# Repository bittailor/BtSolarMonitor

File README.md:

# IoT Solar Monitor

Work in progress for my [Open IoT Challenge 2.0 project](http://open-iot-challenge.bittailor.ch/edition/second/)

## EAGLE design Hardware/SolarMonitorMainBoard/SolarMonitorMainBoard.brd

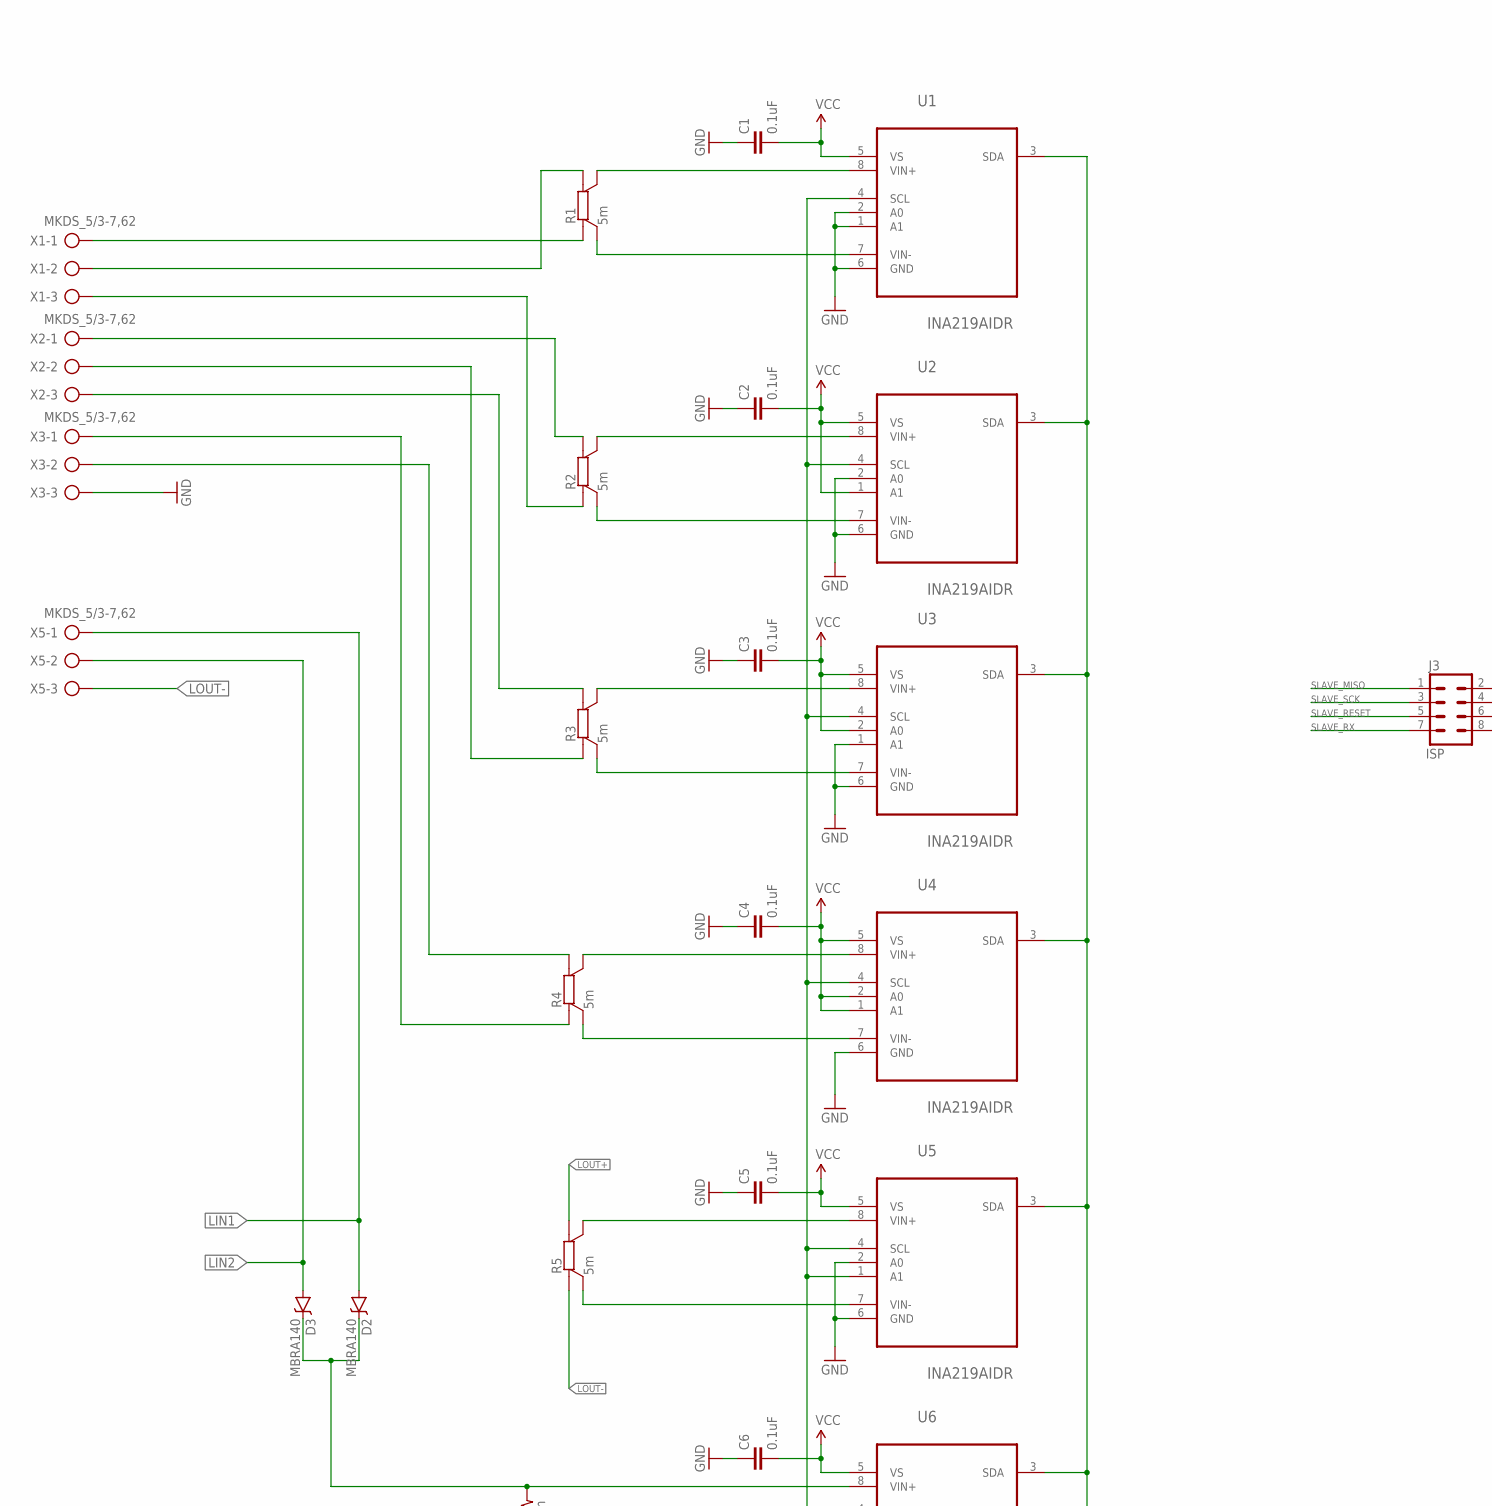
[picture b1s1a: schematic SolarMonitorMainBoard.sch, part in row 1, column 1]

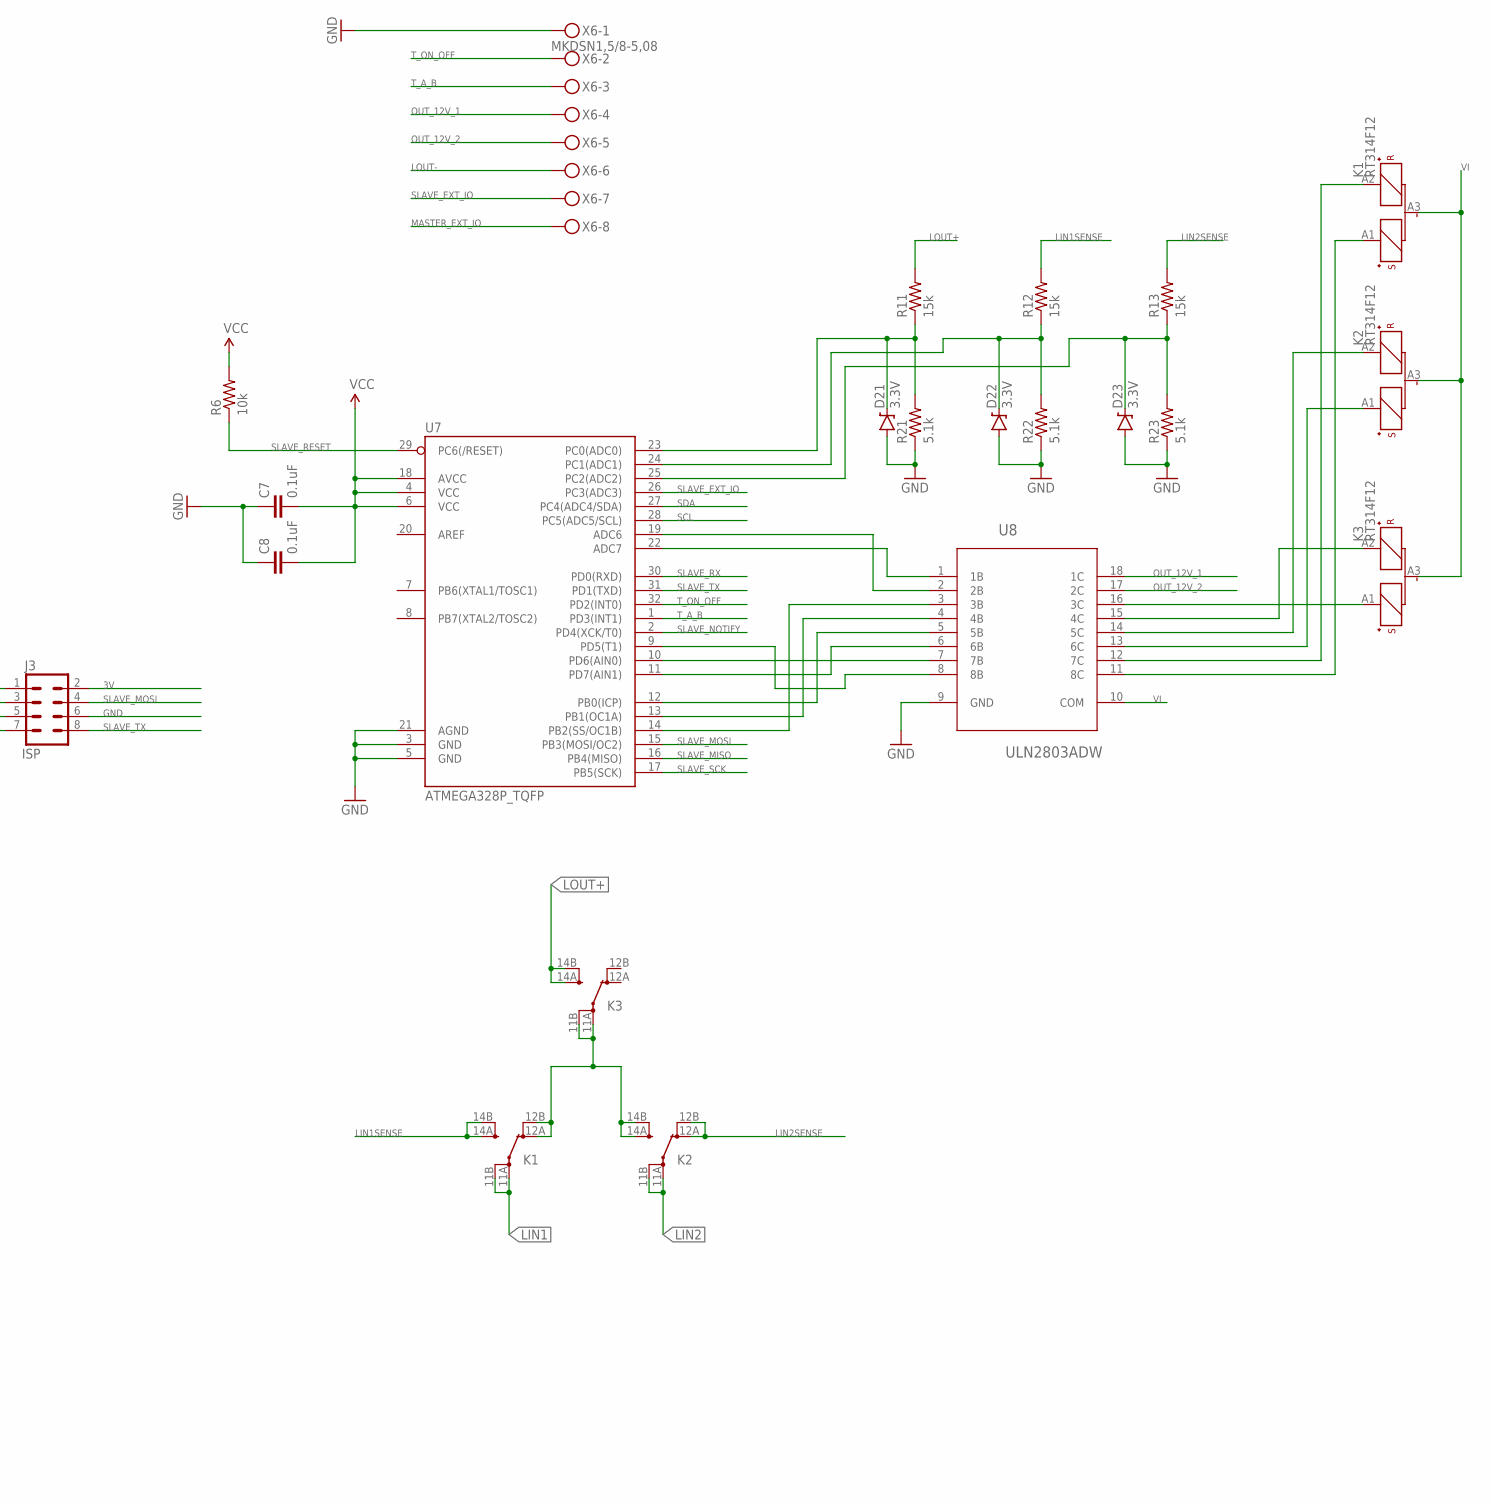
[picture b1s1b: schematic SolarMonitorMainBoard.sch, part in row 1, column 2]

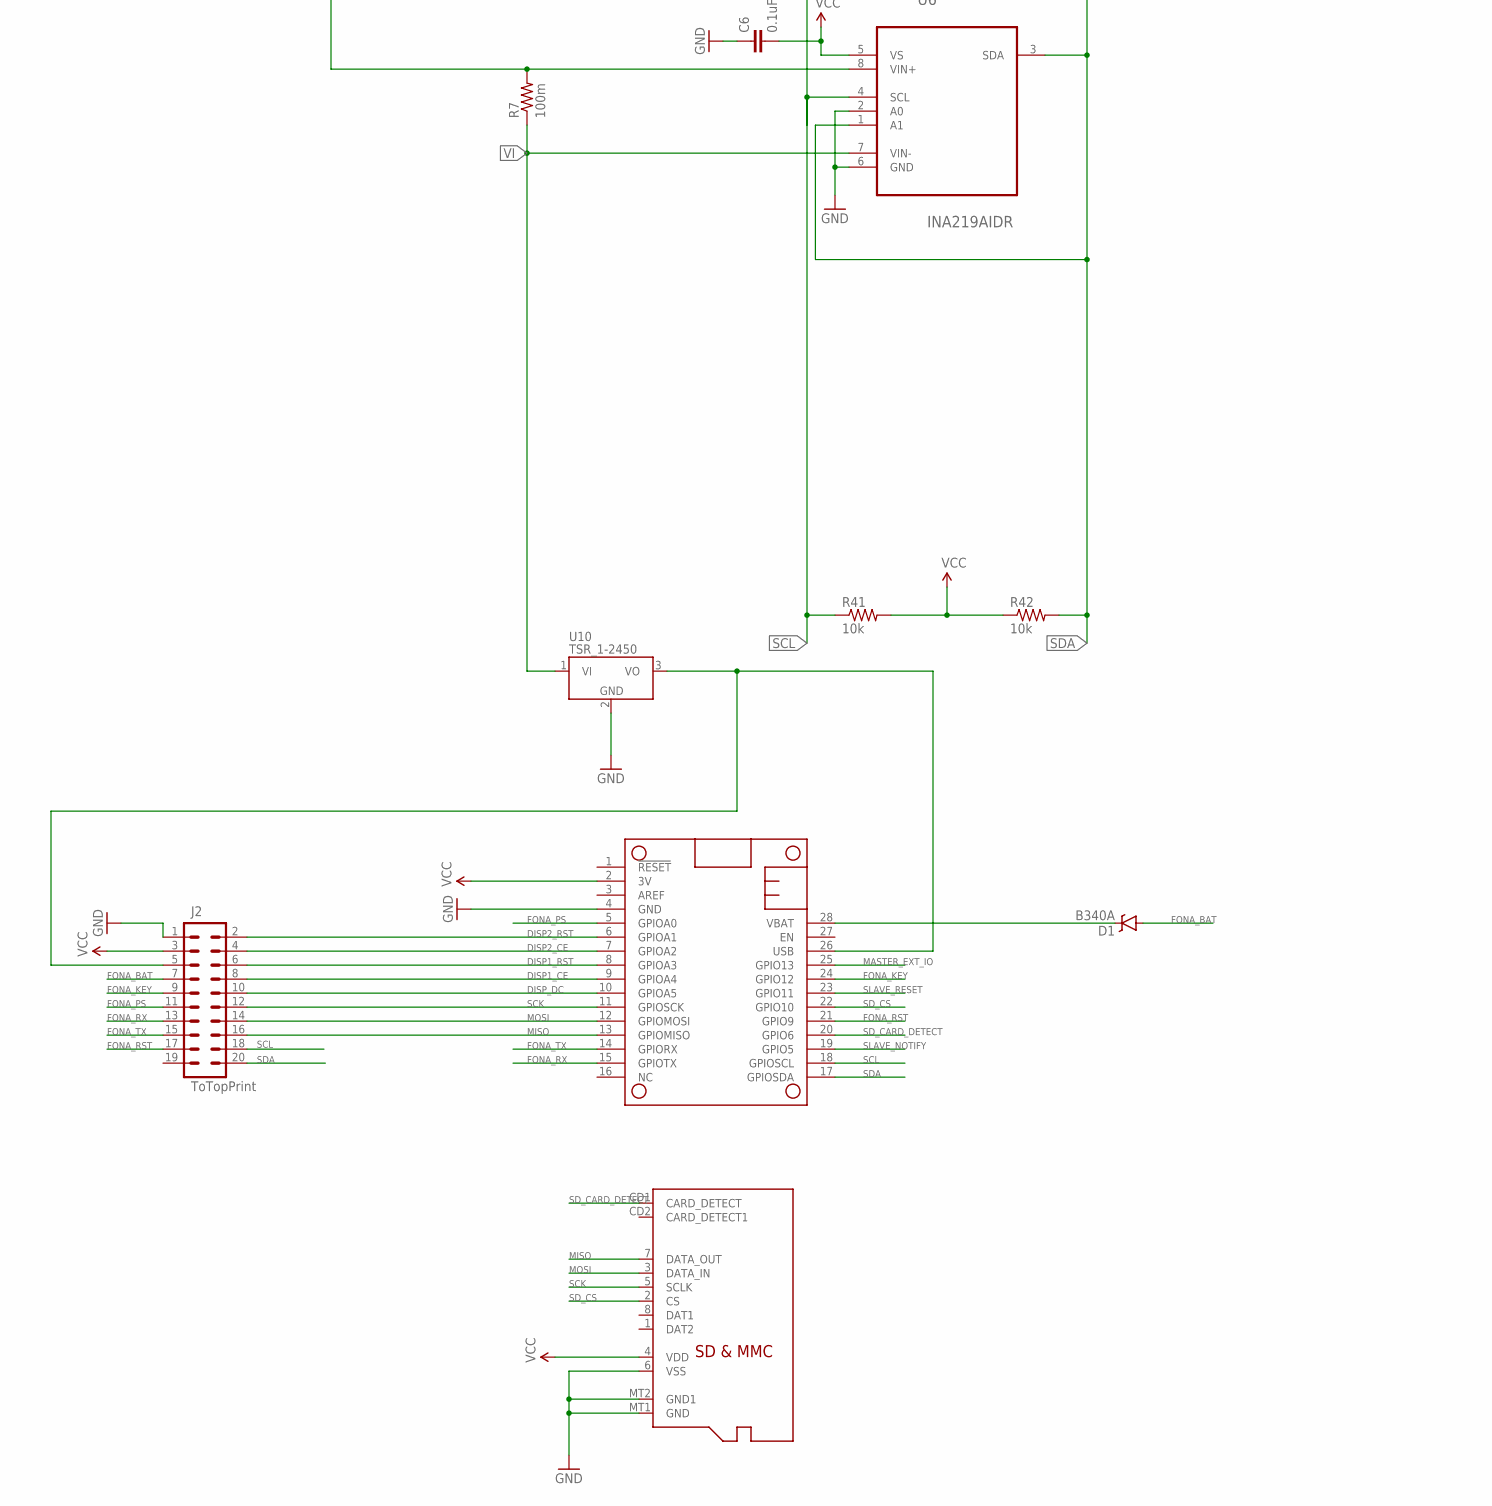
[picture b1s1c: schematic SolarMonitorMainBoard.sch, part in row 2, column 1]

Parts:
C1, C2, C3, C4, C5, C6, C7, C8: 0.1uF; 0805
D1: B340A; SMA-DIODE
D2, D3: MBRA140; SMA-DIODE
D21, D22, D23: 3.3V; SOD-323
J2: ToTopPrint; 2X10
J3: ISP; 2X4
K1, K2, K3: RT314F12; RT1-BI
MS1: FEATHERWING_NODIM; FEATHERWING_DIM
R1, R2, R3, R4, R5: 5m; SMV
R6, R41, R42: 10k; 0805
R7: 100m; R2512
R11, R12, R13: 15k; 0805
R21, R22, R23: 5.1k; 0805
U1, U2, U3, U4, U5, U6: INA219AIDR; SOIC127P600X175-8N
U7: ATMEGA328P_TQFP; TQFP32-08
U8: ULN2803ADW; SOIC127P1030X265-18N
U10: TSR_1-2450; TSR-1
U$1: MICROSD
X1, X2, X3, X5: MKDS_5/3-7,62; MKDS_5/3-762
X6: MKDSN1,5/8-5,08

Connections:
1VIN+: R1.I1 (A), X1.2
1VIN-: R1.I2 (B), X1.1
3V: C1.2, C2.2, C3.2, C4.2, C5.2, C6.2, C7.2, C8.2, J2.3, J3.2, MS1.2 (3V), R6.2, R41.2, R42.1, U1.5 (VS), U2.1 (A1), U2.5 (VS), U3.2 (A0), U3.5 (VS), U4.1 (A1), U4.2 (A0), U4.5 (VS), U5.5 (VS), U6.5 (VS), U7.4 (VCC), U7.6 (VCC), U7.18 (AVCC), U$1.4 (VDD)
5V: J2.5, MS1.26 (USB), U10.3 (VO)
DISP1_CE: J2.8, MS1.9 (GPIOA4)
DISP1_RST: J2.6, MS1.8 (GPIOA3)
DISP2_CE: J2.4, MS1.7 (GPIOA2)
DISP2_RST: J2.2, MS1.6 (GPIOA1)
DISP_DC: J2.10, MS1.10 (GPIOA5)
FONA_BAT: D1.A, J2.7
FONA_KEY: J2.9, MS1.24 (GPIO12)
FONA_PS: J2.11, MS1.5 (GPIOA0)
FONA_RST: J2.17, MS1.21 (GPIO9)
FONA_RX: J2.13, MS1.15 (GPIOTX)
FONA_TX: J2.15, MS1.14 (GPIORX)
GND: C1.1, C2.1, C3.1, C4.1, C5.1, C6.1, C7.1, C8.1, D21.A, D22.A, D23.A, J2.1, J3.6, MS1.4 (GND), R21.1, R22.1, R23.1, U1.1 (A1), U1.2 (A0), U1.6 (GND), U2.2 (A0), U2.6 (GND), U3.1 (A1), U3.6 (GND), U4.6 (GND), U5.2 (A0), U5.6 (GND), U6.2 (A0), U6.6 (GND), U7.3 (GND), U7.5 (GND), U7.21 (AGND), U8.9 (GND), U10.2 (GND), U$1.6 (VSS), U$1.MT1 (GND), U$1.MT2 (GND1), X3.3, X6.1
LIN1: D2.A, K1.11A (PA), K1.11B (PB), X5.1
LIN1SENSE: K1.14A (SA), K1.14B (SB), R12.2
LIN2: D3.A, K2.11A (PA), K2.11B (PB), X5.2
LIN2SENSE: K2.12A (OA), K2.12B (OB), R13.2
LOUT+: K3.14A (SA), K3.14B (SB), R5.I1 (A), R11.2
LOUT-: R5.I2 (B), X5.3, X6.6
MASTER_EXT_IO: MS1.25 (GPIO13), X6.8
MISO: J2.16, MS1.13 (GPIOMISO), U$1.7 (DATA_OUT)
MOSI: J2.14, MS1.12 (GPIOMOSI), U$1.3 (DATA_IN)
unnamed: R2.I2 (B), X1.3
unnamed: D21.C, R11.1, R21.2, U7.23 (PC0(ADC0))
unnamed: U7.9 (PD5(T1)), U8.8 (8B)
unnamed: R2.I1 (A), X2.1
unnamed: R3.I1 (A), X2.3
unnamed: R3.I2 (B), X2.2
unnamed: R4.I2 (B), X3.1
unnamed: R4.I1 (A), X3.2
unnamed: D2.C, D3.C, R7.2, U6.8 (VIN+)
unnamed: U7.10 (PD6(AIN0)), U8.7 (7B)
unnamed: R2.U1 (SA), U2.8 (VIN+)
unnamed: R2.U2 (SB), U2.7 (VIN-)
unnamed: R1.U1 (SA), U1.8 (VIN+)
unnamed: R1.U2 (SB), U1.7 (VIN-)
unnamed: R3.U1 (SA), U3.8 (VIN+)
unnamed: R3.U2 (SB), U3.7 (VIN-)
unnamed: R4.U1 (SA), U4.8 (VIN+)
unnamed: R4.U2 (SB), U4.7 (VIN-)
unnamed: R5.U1 (SA), U5.8 (VIN+)
unnamed: R5.U2 (SB), U5.7 (VIN-)
unnamed: U7.11 (PD7(AIN1)), U8.6 (6B)
unnamed: K1.12A (OA), K1.12B (OB), K2.14A (SA), K2.14B (SB), K3.11A (PA), K3.11B (PB)
unnamed: U7.12 (PB0(ICP)), U8.5 (5B)
unnamed: U7.13 (PB1(OC1A)), U8.4 (4B)
unnamed: U7.14 (PB2(SS/OC1B)), U8.3 (3B)
unnamed: U7.22 (ADC7), U8.1 (1B)
unnamed: U7.19 (ADC6), U8.2 (2B)
unnamed: K2.A1 (S+), U8.13 (6C)
unnamed: K2.A2 (R+), U8.14 (5C)
unnamed: D22.C, R12.1, R22.2, U7.24 (PC1(ADC1))
unnamed: D23.C, R13.1, R23.2, U7.25 (PC2(ADC2))
unnamed: K3.A2 (R+), U8.15 (4C)
unnamed: K1.A2 (R+), U8.12 (7C)
unnamed: K1.A1 (S+), U8.11 (8C)
unnamed: K3.A1 (S+), U8.16 (3C)
OUT_12V_1: U8.18 (1C), X6.4
OUT_12V_2: U8.17 (2C), X6.5
SCK: J2.12, MS1.11 (GPIOSCK), U$1.5 (SCLK)
SCL: J2.18, MS1.18 (GPIOSCL), R41.1, U1.4 (SCL), U2.4 (SCL), U3.4 (SCL), U4.4 (SCL), U5.1 (A1), U5.4 (SCL), U6.4 (SCL), U7.28 (PC5(ADC5/SCL))
SDA: J2.20, MS1.17 (GPIOSDA), R42.2, U1.3 (SDA), U2.3 (SDA), U3.3 (SDA), U4.3 (SDA), U5.3 (SDA), U6.1 (A1), U6.3 (SDA), U7.27 (PC4(ADC4/SDA))
SD_CARD_DETECT: MS1.20 (GPIO6), U$1.CD1 (CARD_DETECT)
SD_CS: MS1.22 (GPIO10), U$1.2 (CS)
SLAVE_EXT_IO: U7.26 (PC3(ADC3)), X6.7
SLAVE_MISO: J3.1, U7.16 (PB4(MISO))
SLAVE_MOSI: J3.4, U7.15 (PB3(MOSI/OC2))
SLAVE_NOTIFY: MS1.19 (GPIO5), U7.2 (PD4(XCK/T0))
SLAVE_RESET: J3.5, MS1.23 (GPIO11), R6.1, U7.29 (PC6(/RESET))
SLAVE_RX: J3.7, U7.30 (PD0(RXD))
SLAVE_SCK: J3.3, U7.17 (PB5(SCK))
SLAVE_TX: J3.8, U7.31 (PD1(TXD))
T_A_B: U7.1 (PD3(INT1)), X6.3
T_ON_OFF: U7.32 (PD2(INT0)), X6.2
VBAT: D1.C, MS1.28 (VBAT)
VI: K1.A3 (-), K2.A3 (-), K3.A3 (-), R7.1, U6.7 (VIN-), U8.10 (COM), U10.1 (VI)

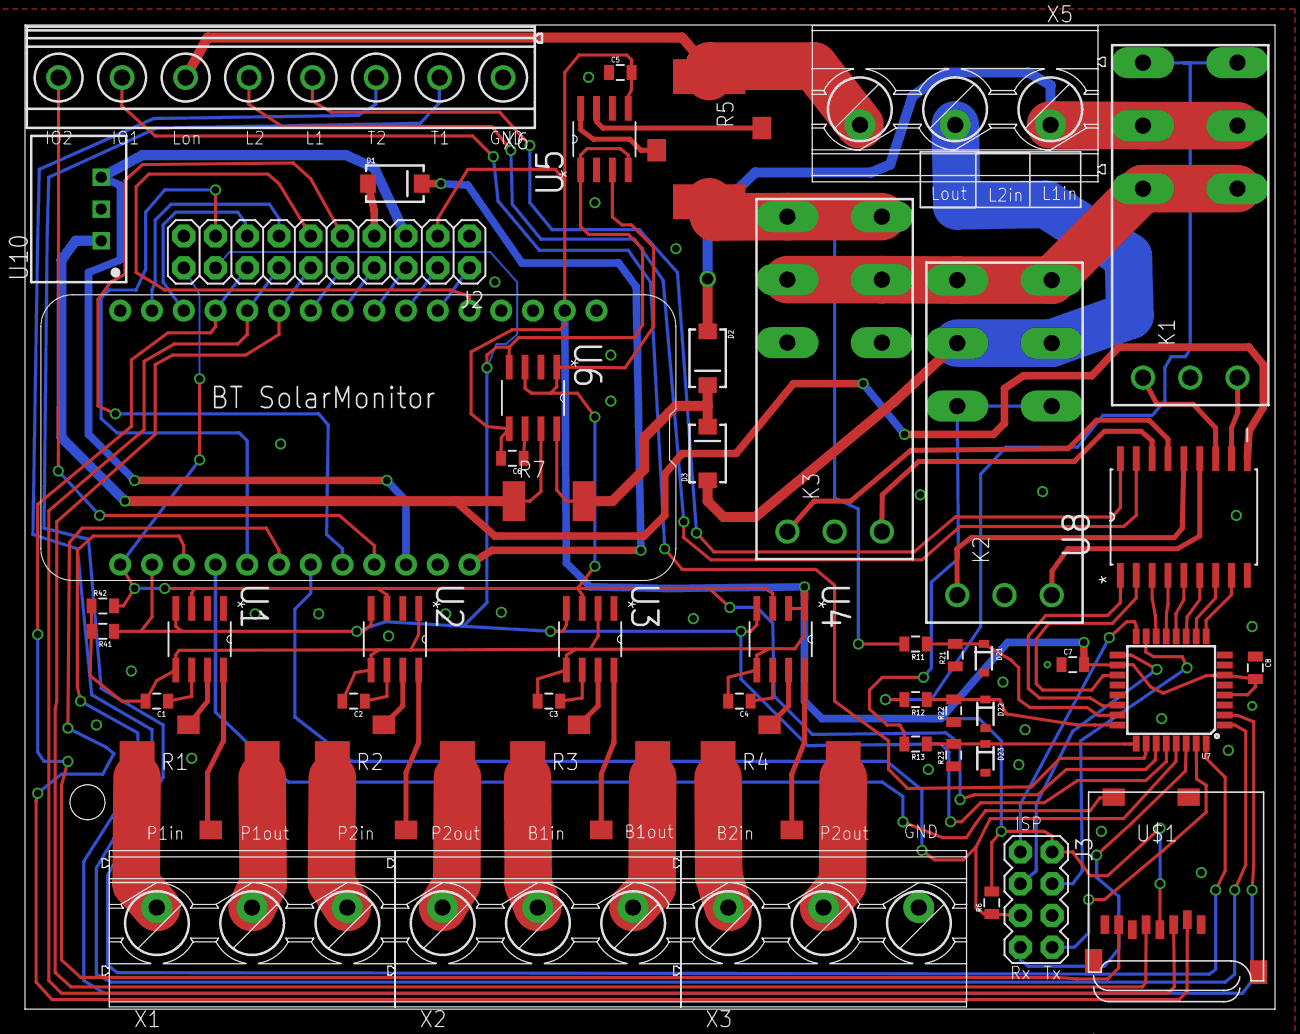
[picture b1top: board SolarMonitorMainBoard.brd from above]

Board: 2 copper layers, 100.0 x 78.7 mm, 51 parts (1 on the bottom side), 79 nets.

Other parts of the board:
U$2: OSHW-LOGO-L

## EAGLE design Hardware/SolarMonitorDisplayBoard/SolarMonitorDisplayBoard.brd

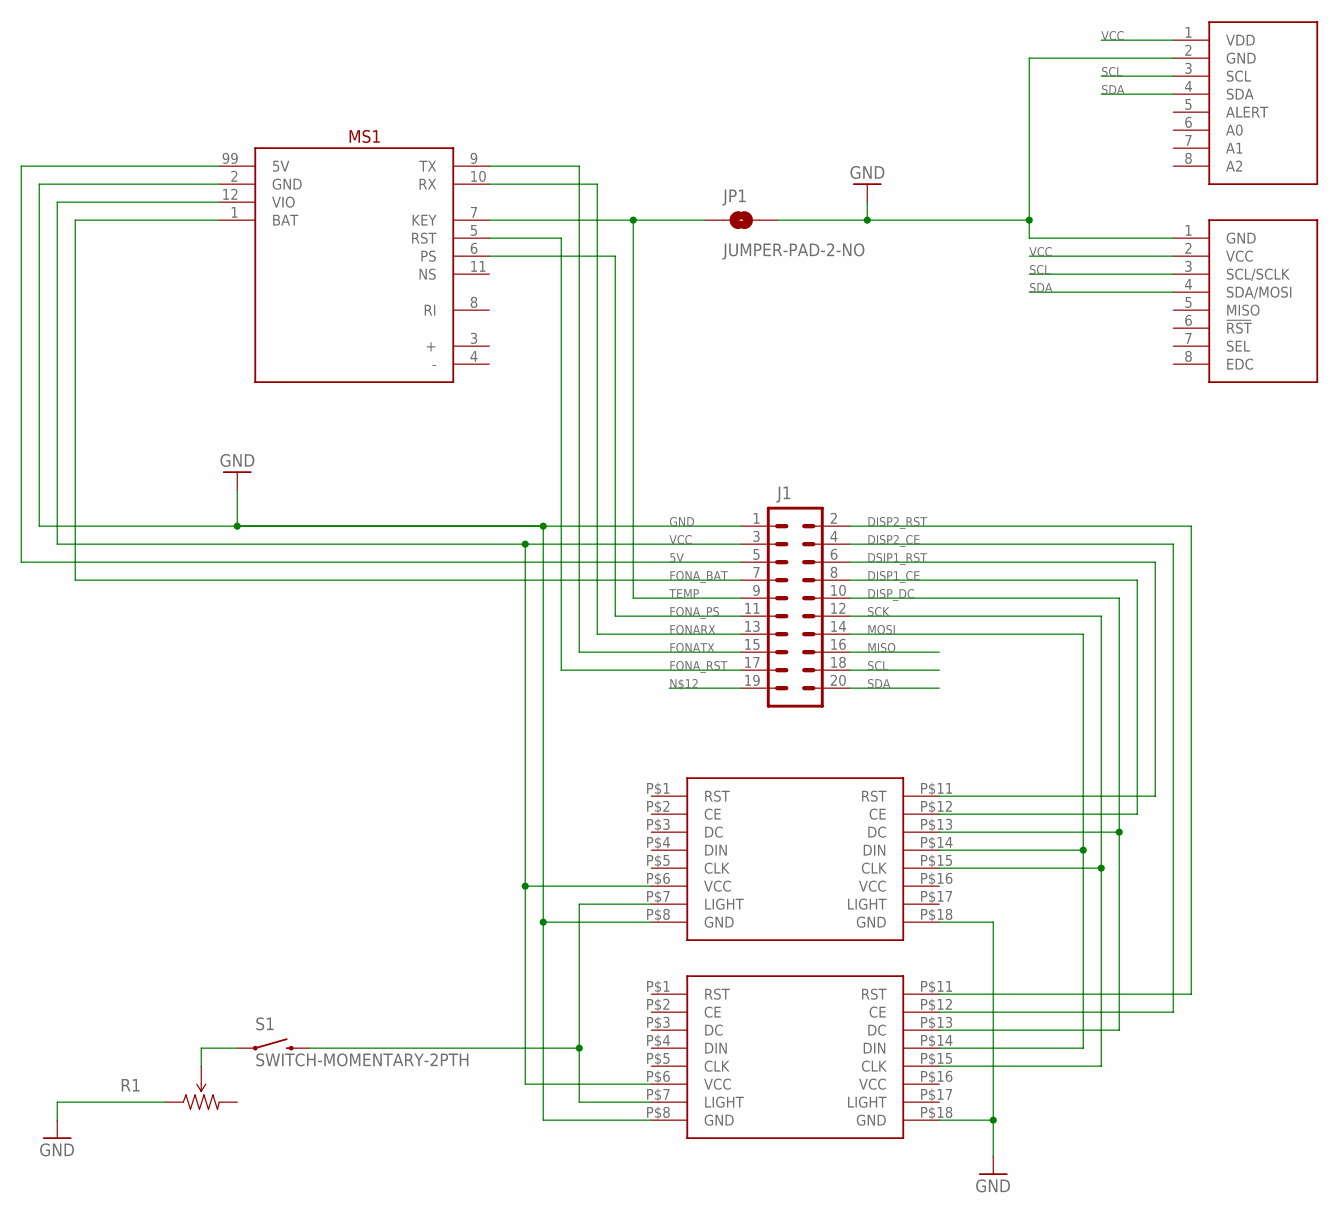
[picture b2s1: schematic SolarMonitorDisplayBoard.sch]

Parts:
BARO: T5403_BREAKOUT
J1: M10X2; 2X10
JP1: JUMPER-PAD-2-NO; PAD-JUMPER-2-NO_NO_SILK
MS1: FONA
R1: TRIMPOTPTH; TRIM_POT_PTH
S1: SWITCH-MOMENTARY-2PTH; TACTILE-PTH
TEMP: MCP9808_BREAKOUT
U$1, U$2: NOKIA_LCD_BREAKOUT

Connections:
5V: J1.5, MS1.99 (5V)
DISP1_CE: J1.8, U$2.P$12 (CE)
DISP2_CE: J1.4, U$1.P$12 (CE)
DISP2_RST: J1.2, U$1.P$11 (RST)
DISP_DC: J1.10, U$1.P$13 (DC), U$2.P$13 (DC)
DSIP1_RST: J1.6, U$2.P$11 (RST)
FONARX: J1.13, MS1.10 (RX)
FONATX: J1.15, MS1.9 (TX)
FONA_BAT: J1.7, MS1.1 (BAT)
FONA_PS: J1.11, MS1.6 (PS)
FONA_RST: J1.17, MS1.5 (RST)
GND: BARO.1 (GND), J1.1, JP1.2, MS1.2 (GND), R1.1 (CCW), TEMP.2 (GND), U$1.P$8 (GND), U$1.P$18 (GND), U$2.P$8 (GND), U$2.P$18 (GND)
MISO: J1.16
MOSI: J1.14, U$1.P$14 (DIN), U$2.P$14 (DIN)
unnamed: R1.2 (WIPER), S1.1
unnamed: S1.3 (2), U$1.P$7 (LIGHT), U$2.P$7 (LIGHT)
SCK: J1.12, U$1.P$15 (CLK), U$2.P$15 (CLK)
SCL: BARO.3 (SCL/SCLK), J1.18, TEMP.3 (SCL)
SDA: BARO.4 (SDA/MOSI), J1.20, TEMP.4 (SDA)
TEMP: J1.9, JP1.1, MS1.7 (KEY)
VCC: BARO.2 (VCC), J1.3, MS1.12 (VIO), TEMP.1 (VDD), U$1.P$6 (VCC), U$2.P$6 (VCC)

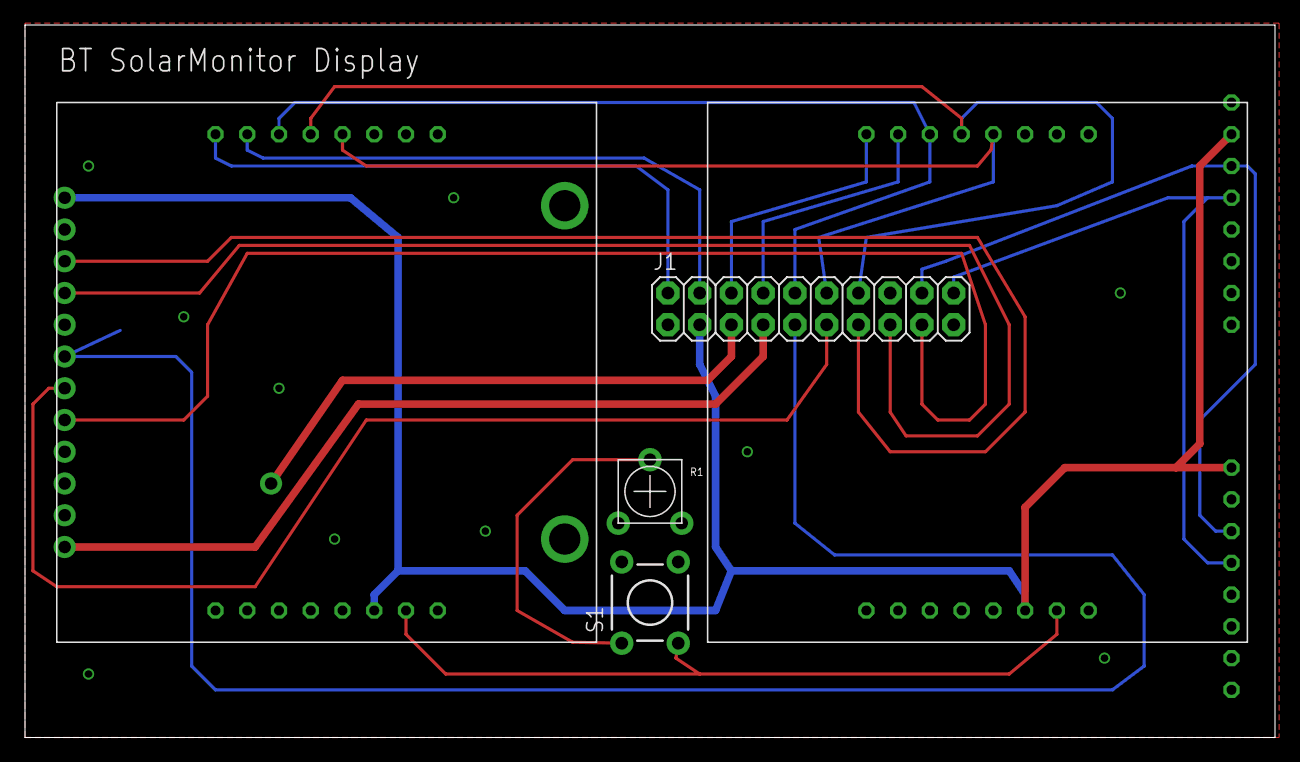
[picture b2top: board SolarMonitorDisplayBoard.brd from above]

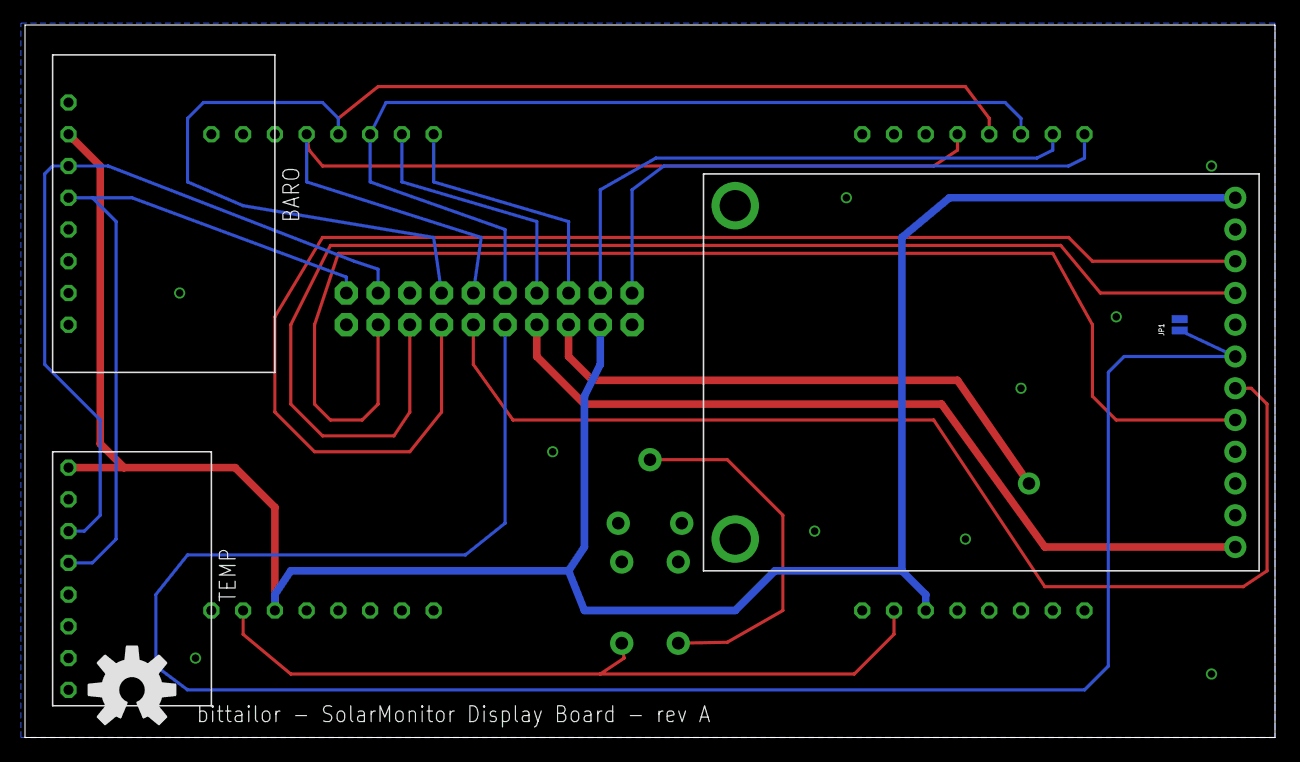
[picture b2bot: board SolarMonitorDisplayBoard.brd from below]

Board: 2 copper layers, 100.0 x 57.0 mm, 10 parts (5 on the bottom side), 20 nets.

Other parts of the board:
U$3: OSHW-LOGO-L

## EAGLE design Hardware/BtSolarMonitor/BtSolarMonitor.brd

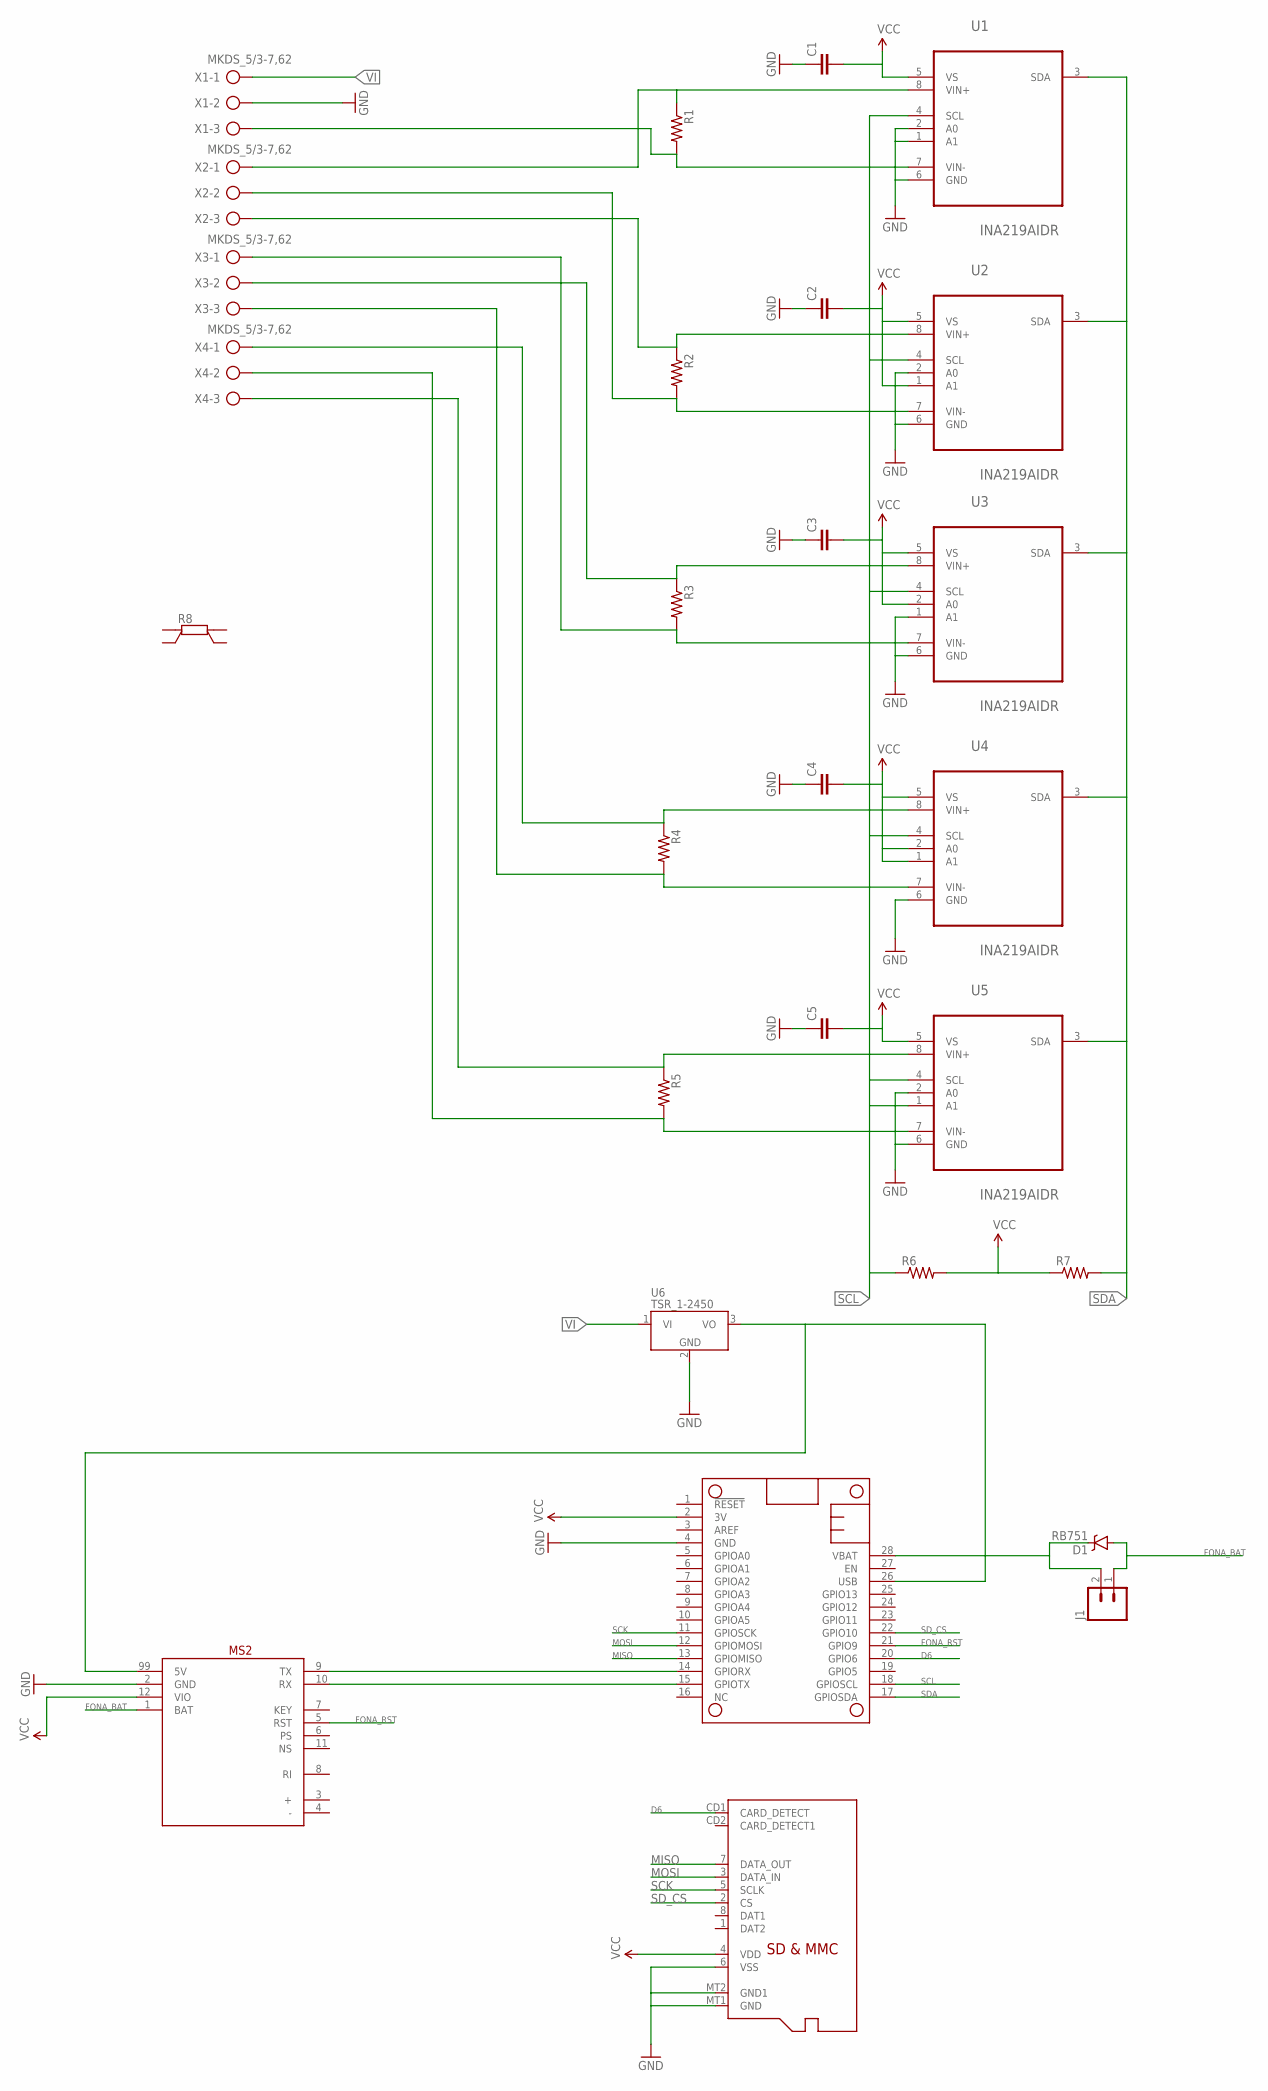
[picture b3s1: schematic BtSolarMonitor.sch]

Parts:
C1, C2, C3, C4, C5: CAP0805; 0805
D1: RB751; SOD-523
J1: M02PTH; 1X02
MS1: FEATHERWING
MS2: FONA
R1, R2, R3, R4, R5: R-US_R2512; R2512
R6, R7: RESISTOR0805-RES; 0805
R8: SMV
U1, U2, U3, U4, U5: INA219AIDR; SOIC127P600X175-8N
U6: TSR_1-2450; TSR-1
U$1: MICROSD
X1, X2, X3, X4: MKDS_5/3-7,62; MKDS_5/3-762

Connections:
1VIN+: R1.1, U1.8 (VIN+), X2.1
1VIN-: R1.2, U1.7 (VIN-), X1.3
5V: MS1.26 (USB), MS2.99 (5V), U6.3 (VO)
D6: MS1.20 (GPIO6), U$1.CD1 (CARD_DETECT)
FONA_BAT: D1.A, J1.1, MS2.1 (BAT)
FONA_RST: MS1.21 (GPIO9), MS2.5 (RST)
GND: C1.1, C2.1, C3.1, C4.1, C5.1, MS1.4 (GND), MS2.2 (GND), U1.1 (A1), U1.2 (A0), U1.6 (GND), U2.2 (A0), U2.6 (GND), U3.1 (A1), U3.6 (GND), U4.6 (GND), U5.2 (A0), U5.6 (GND), U6.2 (GND), U$1.6 (VSS), U$1.MT1 (GND), U$1.MT2 (GND1), X1.2
MISO: MS1.13 (GPIOMISO), U$1.7 (DATA_OUT)
MOSI: MS1.12 (GPIOMOSI), U$1.3 (DATA_IN)
unnamed: R2.2, U2.7 (VIN-), X2.2
unnamed: MS1.15 (GPIOTX), MS2.10 (RX)
unnamed: MS1.14 (GPIORX), MS2.9 (TX)
unnamed: R2.1, U2.8 (VIN+), X2.3
unnamed: R3.1, U3.8 (VIN+), X3.2
unnamed: R3.2, U3.7 (VIN-), X3.1
unnamed: R4.2, U4.7 (VIN-), X3.3
unnamed: R4.1, U4.8 (VIN+), X4.1
unnamed: R5.1, U5.8 (VIN+), X4.3
unnamed: R5.2, U5.7 (VIN-), X4.2
SCK: MS1.11 (GPIOSCK), U$1.5 (SCLK)
SCL: MS1.18 (GPIOSCL), R6.1, U1.4 (SCL), U2.4 (SCL), U3.4 (SCL), U4.4 (SCL), U5.1 (A1), U5.4 (SCL)
SDA: MS1.17 (GPIOSDA), R7.2, U1.3 (SDA), U2.3 (SDA), U3.3 (SDA), U4.3 (SDA), U5.3 (SDA)
SD_CS: MS1.22 (GPIO10), U$1.2 (CS)
VBAT: D1.C, J1.2, MS1.28 (VBAT)
VCC: C1.2, C2.2, C3.2, C4.2, C5.2, MS1.2 (3V), MS2.12 (VIO), R6.2, R7.1, U1.5 (VS), U2.1 (A1), U2.5 (VS), U3.2 (A0), U3.5 (VS), U4.1 (A1), U4.2 (A0), U4.5 (VS), U5.5 (VS), U$1.4 (VDD)
VI: U6.1 (VI), X1.1

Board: 2 copper layers, 28 parts (0 on the bottom side), 26 nets, no tracks yet.

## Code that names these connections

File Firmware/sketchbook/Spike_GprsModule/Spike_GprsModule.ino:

#define FONA_KEY 12
#define FONA_PS A0
#define FONA_RST 9

#include <BtMcuCore.h>
#include <BtMcuNet.h>
#include <MQTTClient.h>

#include <Bt/Core/Logger.hpp>
#include <Bt/Core/Time.hpp>
#include <Bt/Core/DigitalOut.hpp>
#include <Bt/Core/DigitalIn.hpp>
#include <Bt/Core/Workcycle.hpp>
#include <Bt/Core/StaticStringBuilder.hpp>
#include <Bt/Core/PeriodicCallback.hpp>
#include <Bt/Net/Gprs/MobileTerminal.hpp>
#include <Bt/Net/Gprs/GprsModule.hpp>

#include "Spike_GprsModule_Settings.settings.hpp"

const size_t COMMAND_BUFFER_SIZE = 200;
char sCommandBuffer[COMMAND_BUFFER_SIZE] = {0};
bool sRunning = true;
Bt::Core::StaticStringBuilder sCommandBuilder(sCommandBuffer, COMMAND_BUFFER_SIZE);

using namespace Bt;

class PahoTimer {
   public:

      PahoTimer() : mInterval(0), mStart(millis()) {
      }

      PahoTimer(int ms) : mInterval(ms), mStart(millis()) {
      }


      bool expired() {
         return (millis() - mStart) >= mInterval;
      }

      void countdown_ms(unsigned long ms) {
         mInterval = ms;
         mStart = millis();
      }
      void countdown(int seconds) {
         countdown_ms(((unsigned long)seconds) * 1000L);
      }

      int left_ms() {
         unsigned long delay = millis() - mStart;
         if(delay >= mInterval) {
            return 0;
         }
         return mInterval - delay;
      }

   private:
      unsigned long mInterval;
      unsigned long mStart;

};

Core::Time sTime;
Core::DigitalOut sOnOffKey(FONA_KEY);
Core::DigitalOut sReset(FONA_RST);
Core::DigitalIn sPowerState(FONA_PS);
Net::Gprs::MobileTerminal sMobileTerminal(Serial1);
Net::Gprs::GprsModule sGprsModule(sGprsModuleSettings, sTime,sOnOffKey,sReset,sPowerState,sMobileTerminal);
MQTT::Client<Net::Gprs::I_GprsClient, PahoTimer, 500> sMqttClient(sGprsModule);
Core::Workcycle sWorkcycle;


void handleAction(MQTT::MessageData& pMessageData) {
   MQTT::Message& message = pMessageData.message;
   char payload[message.payloadlen + 1];
   memcpy(payload,message.payload,message.payloadlen);
   payload[message.payloadlen] = 0;
   Serial.print("Message ");
   Serial.print(" arrived: qos ");
   Serial.print(message.qos);
   Serial.print(", retained ");
   Serial.print(message.retained);
   Serial.print(", dup ");
   Serial.print(message.dup);
   Serial.print(", packetid ");
   Serial.println(message.id);
   Serial.print("Payload ");
   Serial.println(payload);
}

class Listener : public Net::Gprs::GprsModule::I_Listener {
   public:
      virtual void stateChanged(Net::Gprs::GprsModule::State pState) {
         LOG("stateChanged " << static_cast<int>(pState));
      }

      virtual void onReady() {
         const char * url = MQTT_BROKER;

         int rc = sGprsModule.connect(url,1883);
         if(rc!= 0) {
            LOG("tcp connect failed with " << rc);
         }
      }

      virtual void onConnected() {
         MQTTPacket_connectData data = MQTTPacket_connectData_initializer;
         data.MQTTVersion = 3;
         data.clientID.cstring = (char*)MQTT_CLIENT_ID;
         data.keepAliveInterval = 120;
         data.willFlag = true;
         data.will.topicName.cstring = (char*)"device/state";
         data.will.message.cstring = (char*)"offline";
         data.will.retained = true;
         data.will.qos = MQTT::QOS1;
         data.username.cstring = (char*)MQTT_USERNAME;
         data.password.cstring = (char*)MQTT_PASSWORD;

         int rc = sMqttClient.connect(data);
         if (rc != 0)
         {
            LOG("!!! mqtt connect failed "  << rc);
            sGprsModule.disconnect();
            return;
         }
         LOG("MQTT connected");
         sMqttClient.subscribe("spike/action", MQTT::QOS1, &handleAction);

         rc = publish("device/state","online",MQTT::QOS1,true);
         LOG("MQTT publish returned " << rc);
         mConnected = true;
      }

      virtual void onDisconnected() {
         mConnected = false;
      }

      void publishTime(){
         if(mConnected){
            sMobileTerminal.disableSleepMode();
            sMqttClient.yield(1);
            char msg[30];
            Core::StaticStringBuilder builder(msg,30);
            builder.print(millis());
            int rc = publish("spike/millis",msg, MQTT::QOS1);
            if(rc != 0) {
               LOG("!!! MQTT publish failed " << rc);
            } else {
               LOG("MQTT publish success ");
            }
            sMqttClient.yield(10);
            sMobileTerminal.enableSleepMode();

         }
      }

      int publish(const char* pTopicName, const char* pMessage, MQTT::QoS pQos, bool pRetained = false) {
         LOG("MQTT publish " << pTopicName << " - " << pMessage << " [" << strlen(pMessage) << "]" );
         return sMqttClient.publish(pTopicName, (void*)pMessage, strlen(pMessage), pQos, pRetained);
      }

      bool mConnected = false;

};

Listener sListener;

//Core::PeriodicCallback sYield(sTime,500,Core::Function<void()>::build<Listener,&Listener::yield>(sListener));
Core::PeriodicCallback sPublish(sTime,50000,Core::Function<void()>::build<Listener,&Listener::publishTime>(sListener));

void setup() {
   pinMode(13, OUTPUT);
   digitalWrite(13, HIGH);
   while (!Serial) {}
   Serial.begin(115200);
   Serial.println(F("** Spike GPRS Module**"));
   Serial1.begin(9600);
   digitalWrite(13, LOW);
   delay(1000);


   sWorkcycle.add(sGprsModule);
   sWorkcycle.add(sPublish);

   sOnOffKey.begin();
   sReset.begin();
   sPowerState.begin();
   sGprsModule.begin(sListener);
}

void loop() {
   sWorkcycle.oneWorkcycle();
   //sMqttClient.yield(10);

   while(Serial.available()) {
      char c = Serial.read();
      if(c == '\n') {
         executeCommand(sCommandBuffer);
         sCommandBuilder.clear();
      } else {
         Serial.print(" ++ Append '");
         Serial.print(c);
         Serial.println("'");
         sCommandBuilder.print(c);
      }
   }

}

void executeCommand(const char* pCommand) {
   if(strcmp("s",pCommand)==0) {
      shutdown();
   }else if(strcmp("shutdown",pCommand)==0) {
      shutdown();
   } else {
      Serial.print("Unknown command: '");
      Serial.print(pCommand);
      Serial.println("'");
   }
}

void shutdown() {
   sRunning = false;
   Serial.println("start shutdown ...");
   sMqttClient.disconnect();
   sGprsModule.disconnect();
   sMobileTerminal.powerDown();
   Serial.println("... shutdown done");
   while (true) {
      Serial.println("Ready to reboot ...");
      delay(2000);
   }
}

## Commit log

2016-01-23 initial import
2016-01-23 First draft of ResourceCheck sketch
2016-02-15 Prefix all the sketches to test out things with Spike_
2016-02-15 Add some dependencies trough submodules.
2016-02-15 Add Adafruit-PCD8544-Nokia-5110-LCD-library as submodule dependency since it needs some tweaks to support multiple instances.
2016-02-15 reorganize folder structure
2016-02-15 Rename main board
2016-02-15 Ignore for eagle project file
2016-02-15 Work in progress on the main board ...
2016-02-15 Update ignores for eagle stuff.
2016-02-15 Update schematic
2016-02-15 Lets hope
2016-02-15 Before autoroute try
2016-02-17 Schematic done. Lets route ...
2016-02-17 Some Routing
2016-02-17 Fix checks
2016-02-18 More routing
2016-02-18 All routed. Let's check.
2016-02-18 Fix Warnings ADD I2C to header
2016-02-18 Cleanup
2016-02-19 Replace BAT schottky with SMA part.
2016-02-20 Schematic for display PCB
2016-02-20 Add some labels.
2016-02-22 Add trim pot and button for background light.
2016-03-07 Work in progress.
2016-03-19 work in progress
2016-03-31 Coding and testing the SlaveIO StateMachine
2016-03-31 Fix ground instead of +12V error in schematic routing on board not done yet.
2016-03-31 Add rake clean
2016-03-31 Remove unused flag
2016-03-31 Let's try to use travis.ci
2016-03-31 Trigger Travis.ci
2016-03-31 Next try with Travis.ci
2016-03-31 Travis install rake.
2016-03-31 Skip the arduino stuff till host test run
2016-03-31 Fix rake call
2016-03-31 Also install the dependencies.
2016-03-31 use ninja from path
2016-03-31 No c++11 since Travis.ci has an old Gcc
2016-03-31 Change to using Trusty
2016-03-31 Reenable -std=c++11
2016-03-31 Use -pthread for the rather old gcc of travis
2016-03-31 try install new gcc
2016-03-31 Next try
2016-03-31 Try the matrix
2016-03-31 Revert to running stage
2016-03-31 Build status in README
2016-03-31 Continue implement SlaveController
2016-04-16 Continue implement
    - SlaveController
    - CurrentSensors
2016-04-16 - Rename library - Build for multiple libraries.
2016-04-17 Continue implement main controller
2016-04-21 Implement the master controller and slave I2C
2016-04-21 First attend for I2C with sleep
2016-04-21 sleeping slave that works with I2C
2016-04-29 Work in progress ...
2016-05-19 working
2016-05-20 Combine setup stuff
2016-05-27 working ...
2016-06-01 still working on the AT GPRS module stuff
2016-07-24 Just some more work in progress
2016-07-25 Currently only working for the target
2016-08-01 Hacking the host build to work again.
2016-08-01 Cleanup some stuff.
2016-08-05 Working on GSM connection state display.
2016-08-10 Shutdown for development. Average for publish.
2016-08-11 Clean up screen drawing and development shutdown.
2016-08-11 Fix file casing.
2016-08-11 Travis - try to use newer gcc
2016-08-11 Fix min max macro issue.
2016-08-12 Try coverage.
2016-08-12 Also filter linux system headers for coverage
2016-08-12 Fix file paths for coverage.
2016-08-12 Fix wrong coverage file path
2016-08-12 Remove mocks from coverage.
2016-08-12 Implement state update on screen form GPRS module and MQTT client.
2016-08-13 Improve connection layout.
2016-08-14 Start extracting configuration settings
2016-08-15 extracting configuration settings.
2016-08-16 remove some commented code
2016-09-16 Implement sleep mode for GPRS module.
2016-10-21 Send battery state to IO slave
2016-10-22 Change ON-OFF button logic to be a switch instead of a push-button
2016-10-23 Clean coverage files before running the tests
2016-10-23 Fix unit tests.
2018-08-02 Just add all the stuff
2018-08-02 try to fix travis
2018-08-02 Let's try again
2018-08-02 Just a test
2018-08-02 try to fix link issue on travis
2018-08-02 fix linking of libraries => reverse order

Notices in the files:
parts and their libraries:
SparkFun-Capacitors: Licensing: Creative Commons ShareAlike 4.0 International - https://creativecommons.org/licenses/by-sa/4.0
